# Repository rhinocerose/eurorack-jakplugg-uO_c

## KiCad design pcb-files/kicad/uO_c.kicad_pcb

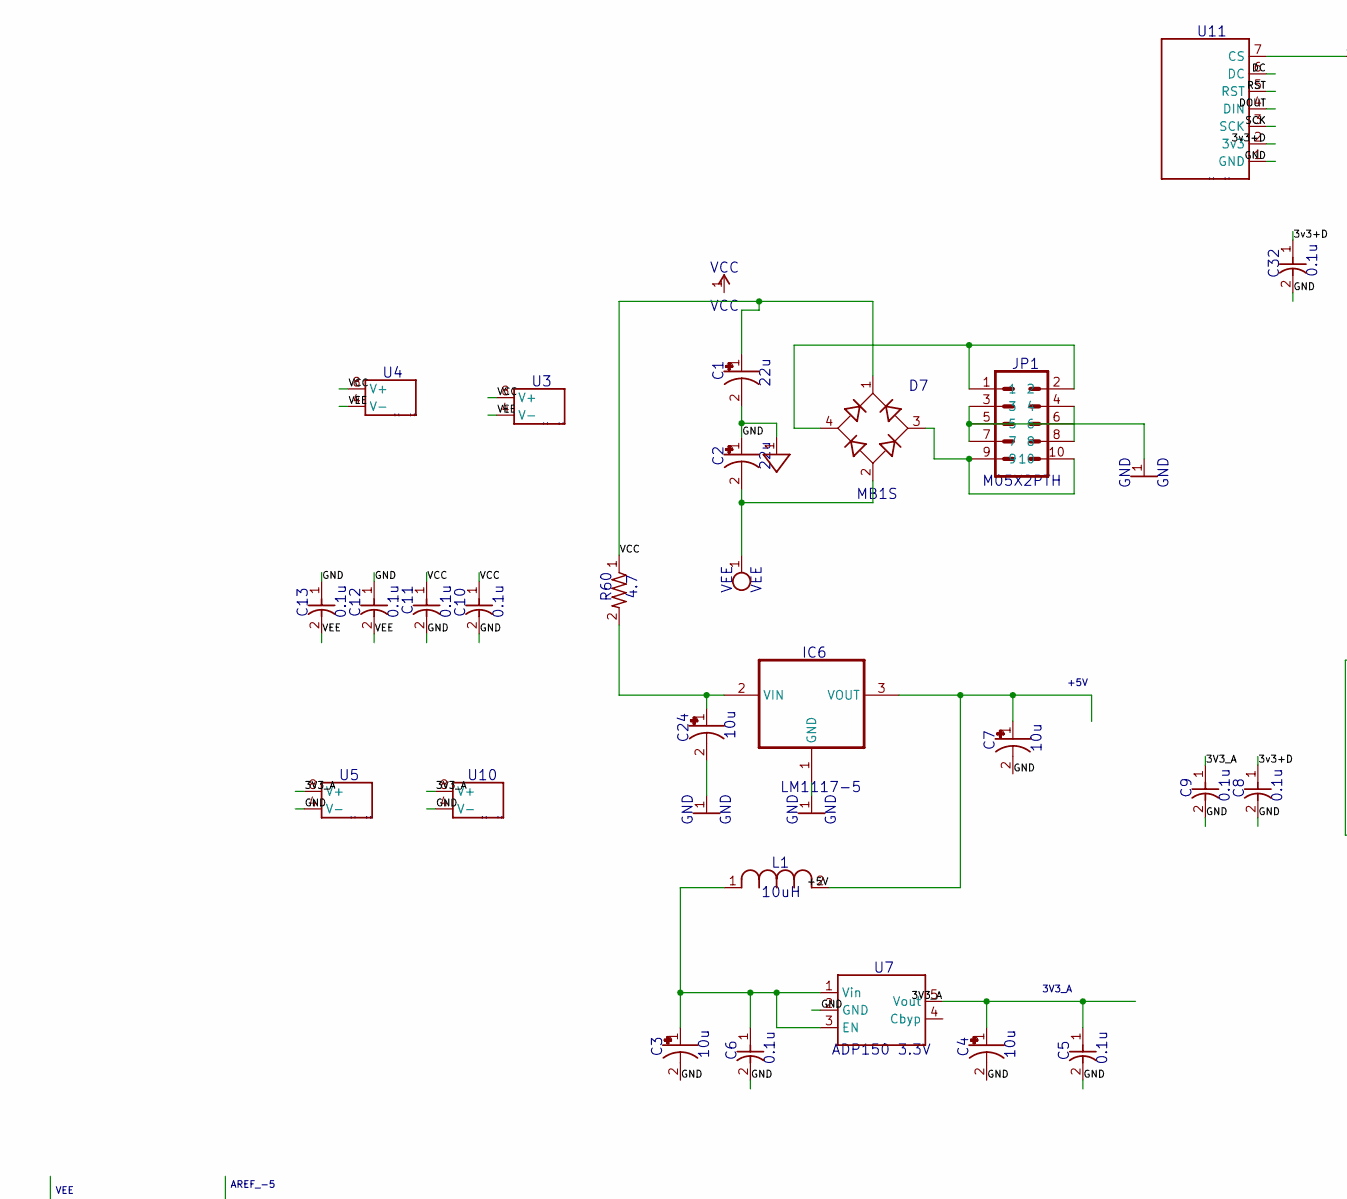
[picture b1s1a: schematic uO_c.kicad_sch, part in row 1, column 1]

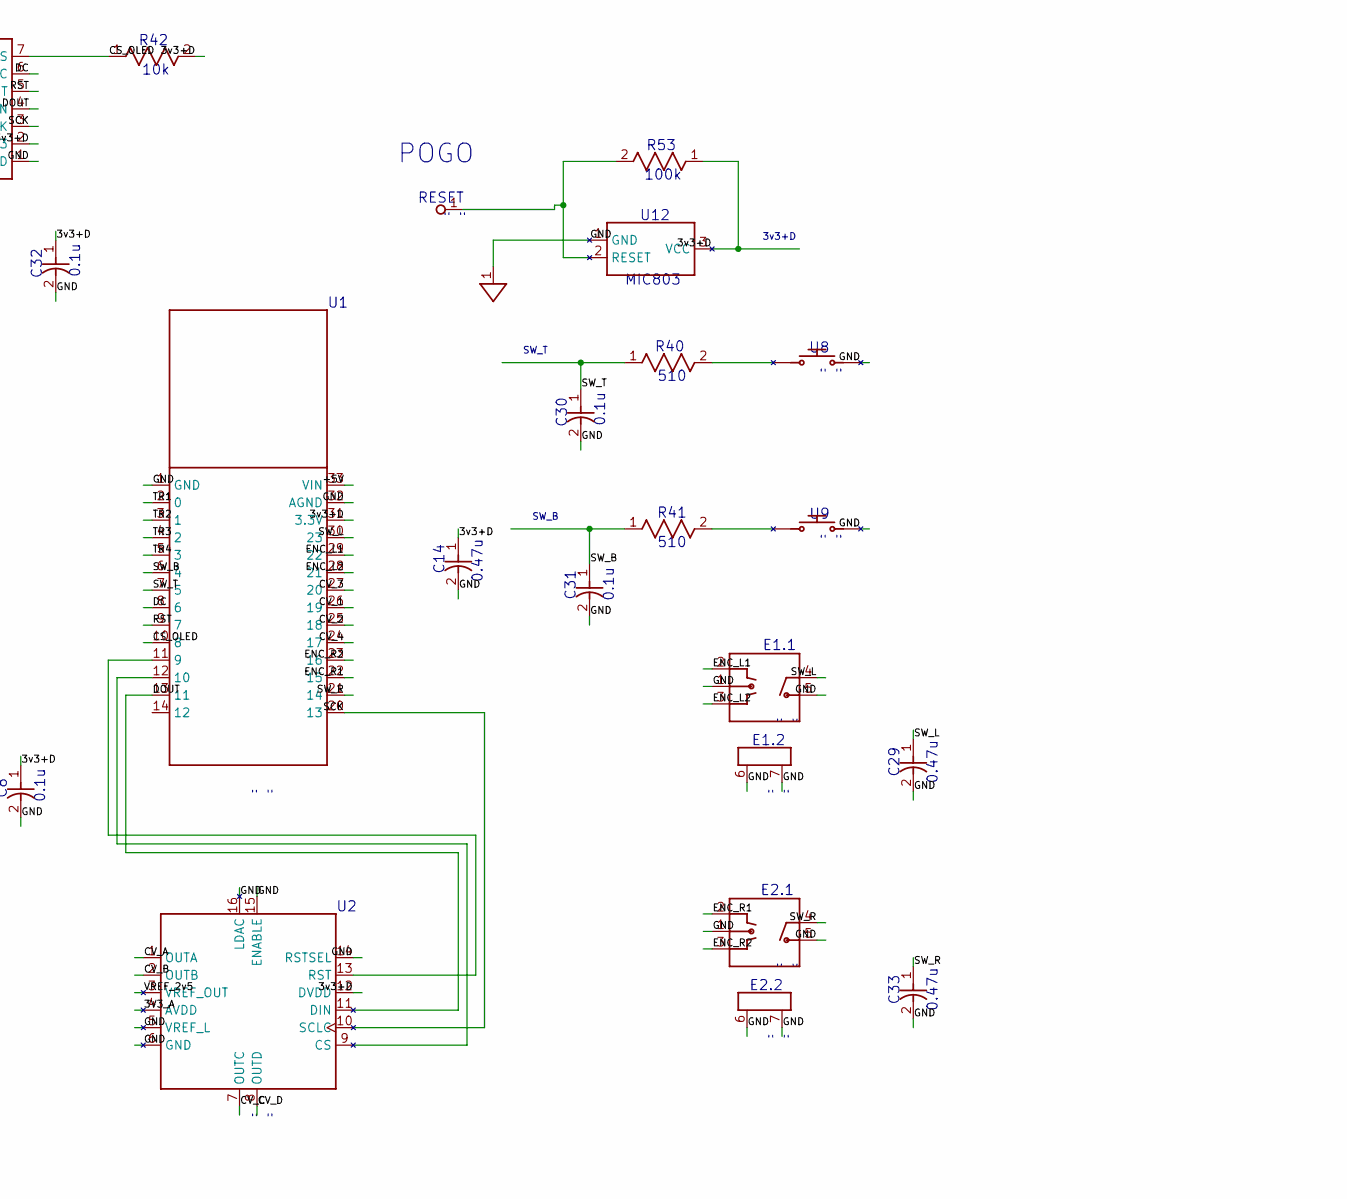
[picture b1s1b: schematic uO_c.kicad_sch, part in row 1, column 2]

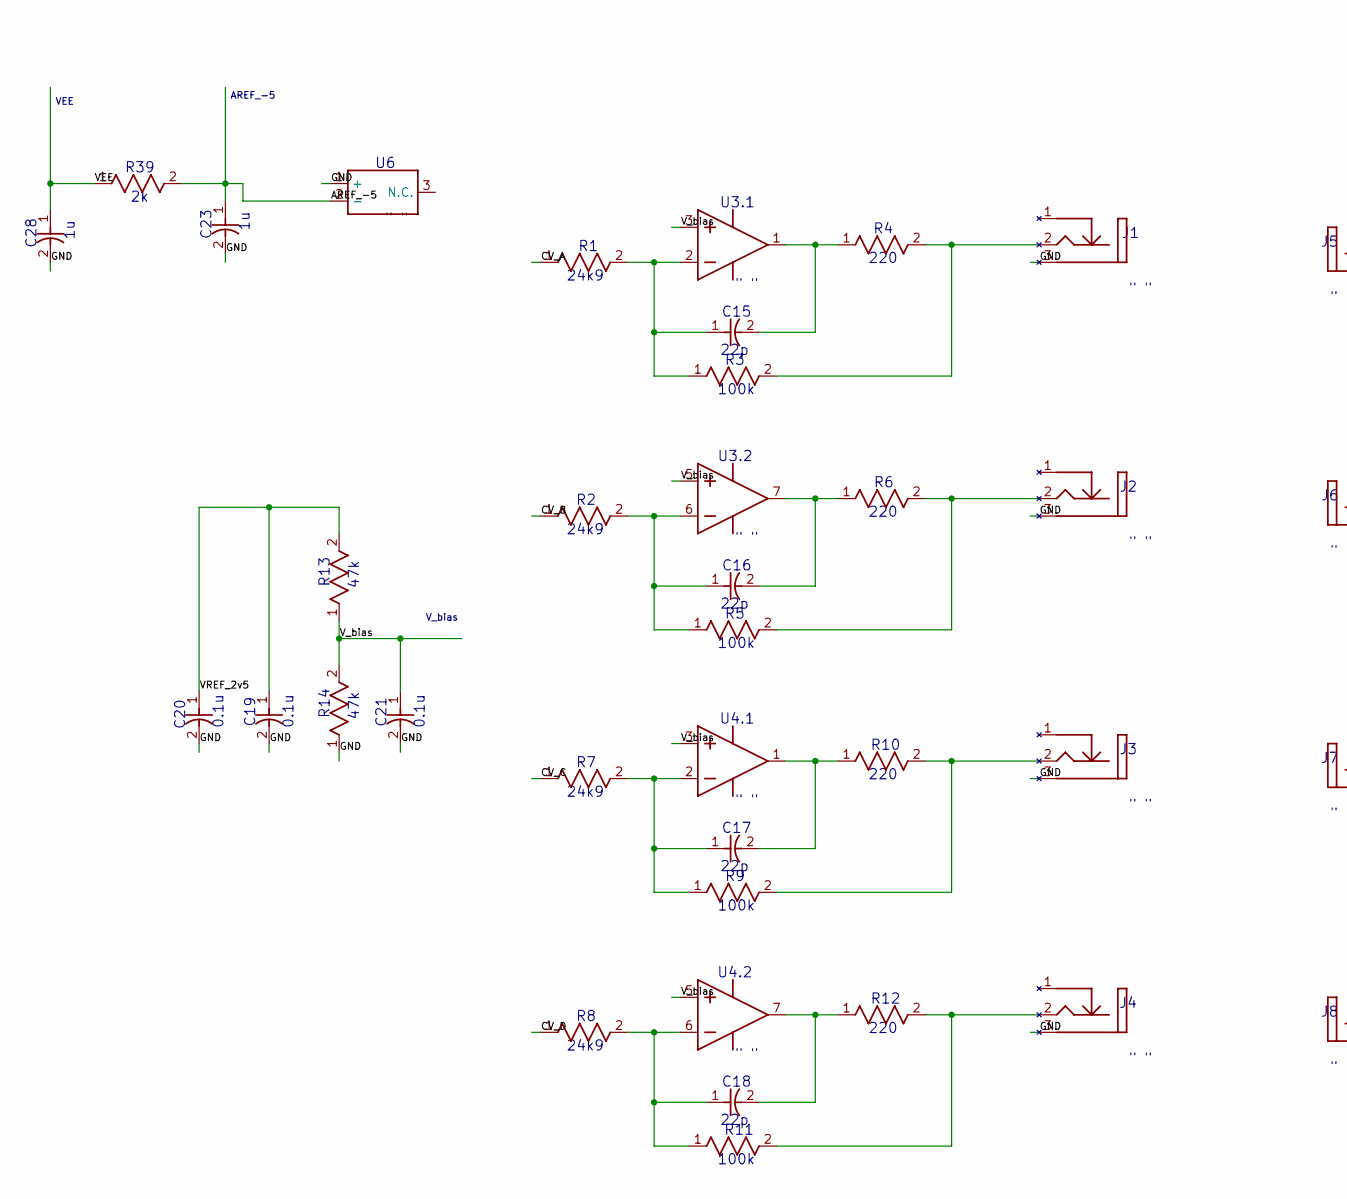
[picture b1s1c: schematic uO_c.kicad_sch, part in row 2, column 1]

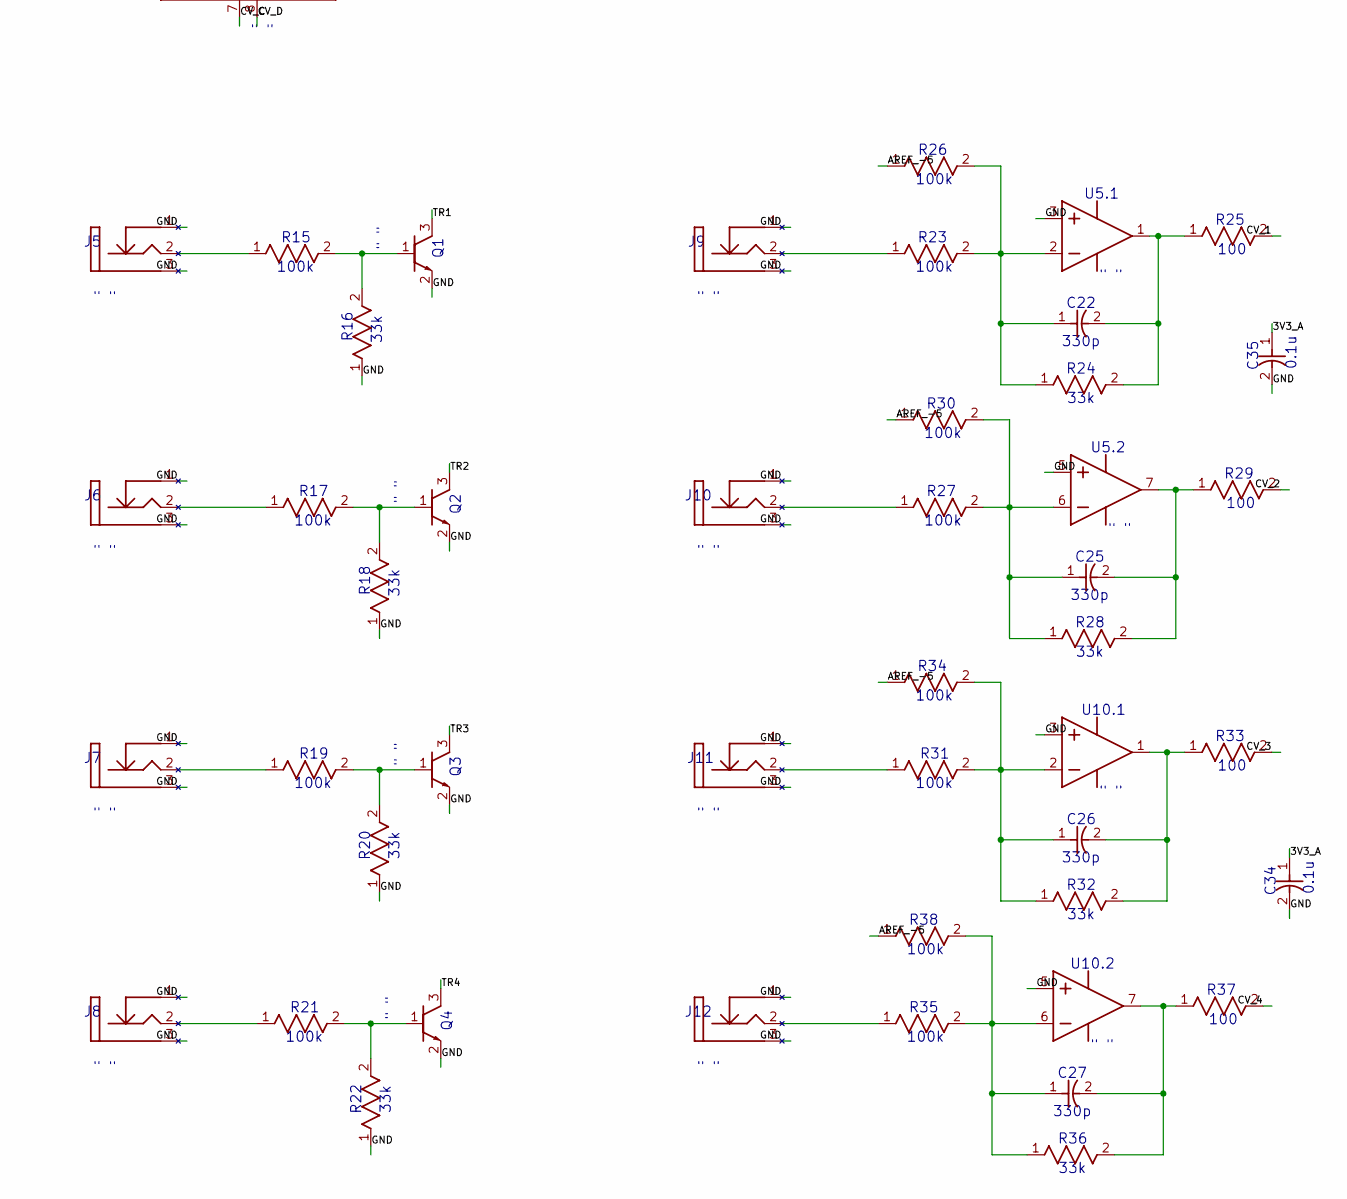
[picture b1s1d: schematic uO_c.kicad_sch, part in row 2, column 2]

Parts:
C1, C2: 22u; CAPAE-5.3X5.3H3
C3, C4, C7, C24: 10u; CAPAE-5.3X5.3H3
C5, C6, C8, C9, C10, C11, C12, C13, C19, C20, C21, C30, C31, C32, C34, C35: 0.1u; CAP_0805
C14, C29, C33: 0.47u; CAP_0805
C15, C16, C17, C18: 22p; CAP_0805
C22, C25, C26, C27: 330p; CAP_0805
C23, C28: 1u; CAP_0805
D7: MB1S; SOP-4_6.5X2.54
E1, E2: PEC11
IC6: LM1117-5; TO252
J1, J2, J3, J4: THONKICONN; THONKICONN_JACK
J5, J6, J7, J8, J9, J10, J11, J12: THONKICONN_20; THONKICONN_JACK
JP1: M05X2PTH; AVR_ICSP
L1: 10uH; RES_1210
Q1, Q2, Q3, Q4: MMBT3904; SOT23
R1, R2, R7, R8: 24k9; RES_0805
R3, R5, R9, R11, R15, R17, R19, R21, R23, R26, R27, R30, R31, R34, R35, R38, R53: 100k; RES_0805
R4, R6, R10, R12: 220; RES_0805
R13, R14: 47k; RES_0805
R16, R18, R20, R22, R24, R28, R32, R36: 33k; RES_0805
R25, R29, R33, R37: 100; RES_0805
R39: 2k; RES_0805
R40, R41: 510; RES_0805
R42: 10k; RES_0805
R60: 4.7; R1206
RESET0: RESET; ROUND-ROUND
U1: TEENSY_3.1_EDGE; TEENSY3.1_EDGE
U2: DAC8565; TSSOP-16
U3, U4: OPA2172; SOIC-8_150MIL
U5, U10: MCP6002; SOIC-8_150MIL
U6: LM4040_EM3-5.0; SOT23
U7: ADP150 3.3V; SOT23-5
U8, U9: 6MM_TACTILE_SW; TL1105SP
U11: 1306_DISP_O_C
U12: MIC803; SOT23

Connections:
3V3_A: C4.1 (+), C5.1, C9.1, C34.1, C35.1, U2.4 (AVDD), U5.8 (V+), U7.5 (Vout), U10.8 (V+)
3v3+D: C8.1, C14.1, C32.1, R42.2, R53.1, U1.31 (3.3V), U2.12 (DVDD), U11.2 (3v3), U12.3 (VCC)
+5V: C7.1 (+), IC6.3 (VOUT), L1.2, U1.33 (VIN)
AREF_-5: C23.1, R26.1, R30.1, R34.1, R38.1, R39.2, U6.2 (-)
CS_DAC: U1.12 (10), U2.9 (CS)
CS_OLED: R42.1, U1.10 (8), U11.7 (CS)
CV_1: R25.2, U1.26 (19)
CV_2: R29.2, U1.25 (18)
CV_3: R33.2, U1.27 (20)
CV_4: R37.2, U1.24 (17)
CV_A: R1.1, U2.1 (OUTA)
CV_B: R2.1, U2.2 (OUTB)
CV_C: R7.1, U2.7 (OUTC)
CV_D: R8.1, U2.8 (OUTD)
DC: U1.8 (6), U11.6 (DC)
DOUT: U1.13 (11), U2.11 (DIN), U11.4 (DIN)
ENC_L1: E1.2, U1.29 (22)
ENC_L2: E1.3, U1.28 (21)
ENC_R1: E2.2, U1.22 (15)
ENC_R2: E2.3, U1.23 (16)
unnamed: D7.3 (AC2), JP1.9, JP1.10
Net_0: J2.2 (Tip), R5.2, R6.2
Net_1: C16.1, R2.2, R5.1, U3.6 (IN-)
Net_2: C16.2, R6.1, U3.7 (OUT)
Net_3: J3.2 (Tip), R9.2, R10.2
Net_4: C17.1, R7.2, R9.1, U4.2 (IN-)
Net_5: C17.2, R10.1, U4.1 (OUT)
Net_6: J4.2 (Tip), R11.2, R12.2
Net_7: C18.1, R8.2, R11.1, U4.6 (IN-)
Net_8: C18.2, R12.1, U4.7 (OUT)
Net_9: Q2.1 ((B)), R17.2, R18.2
Net_10: Q3.1 ((B)), R19.2, R20.2
Net_11: Q4.1 ((B)), R21.2, R22.2
Net_12: C25.1, R27.2, R28.1, R30.2, U5.6 (IN-)
Net_13: C3.1 (+), C6.1, L1.1, U7.1 (Vin), U7.3 (EN)
Net_18: C26.1, R31.2, R32.1, R34.2, U10.2 (IN-)
Net_19: J1.2 (Tip), R3.2, R4.2
Net_20: C15.1, R1.2, R3.1, U3.2 (IN-)
Net_21: C15.2, R4.1, U3.1 (OUT)
Net_22: C27.1, R35.2, R36.1, R38.2, U10.6 (IN-)
Net_35: Q1.1 ((B)), R15.2, R16.2
Net_39: J8.2 (Tip), R21.1
Net_40: J7.2 (Tip), R19.1
Net_41: J6.2 (Tip), R17.1
Net_42: J5.2 (Tip), R15.1
Net_43: C22.1, R23.2, R24.1, R26.2, U5.2 (IN-)
Net_48: C27.2, R36.2, R37.1, U10.7 (OUT)
Net_49: C26.2, R32.2, R33.1, U10.1 (OUT)
Net_50: C25.2, R28.2, R29.1, U5.7 (OUT)
Net_51: C22.2, R24.2, R25.1, U5.1 (OUT)
Net_52: J9.2 (Tip), R23.1
Net_53: J10.2 (Tip), R27.1
Net_54: J11.2 (Tip), R31.1
Net_55: J12.2 (Tip), R35.1
Net_73: C24.1 (+), IC6.2 (VIN), R60.2
Net_75: R41.2, U9.1, U9.2 (1)
Net_76: R40.2, U8.1, U8.2 (1)
Net_88: R53.2, RESET0.1, U12.2 (RESET)
Net_107: D7.4 (AC1), JP1.1, JP1.2
RST: U1.9 (7), U11.5 (RST)
RST_DAC: U1.11 (9), U2.13 (RST)
SCK: U1.20 (13), U2.10 (SCLC), U11.3 (SCK)
SW_B: C31.1, R41.1, U1.6 (4)
SW_L: C29.1, E1.4, U1.30 (23)
SW_R: C33.1, E2.4, U1.21 (14)
SW_T: C30.1, R40.1, U1.7 (5)
TR1: Q1.3 ((C)), U1.2 (0)
TR2: Q2.3 ((C)), U1.3 (1)
TR3: Q3.3 ((C)), U1.4 (2)
TR4: Q4.3 ((C)), U1.5 (3)
VCC: C1.1 (+), C10.1, C11.1, D7.1 (+), R60.1, U3.8 (V+), U4.8 (V+)
VEE: C2.2 (-), C12.2, C13.2, C28.1, D7.2 (-), R39.1, U3.4 (V-), U4.4 (V-)
VREF_2v5: C19.1, C20.1, R13.2, U2.3 (VREF_OUT)
V_bias: C21.1, R13.1, R14.2, U3.3 (IN+), U3.5 (IN+), U4.3 (IN+), U4.5 (IN+)

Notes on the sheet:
E1.1
220
" "
0.1u
V_bias
U4.2
100k
R34
R60
10u
47k
R35
VCC
33k
R41
GND
U12
E2.1
C30
10uH
R30
VEE
C19
R32
C34
3v3+D
4.7
R22
R11
C26
C21
U11
0.47u
R14
C14
C10
SW_B
22u
R40
100

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
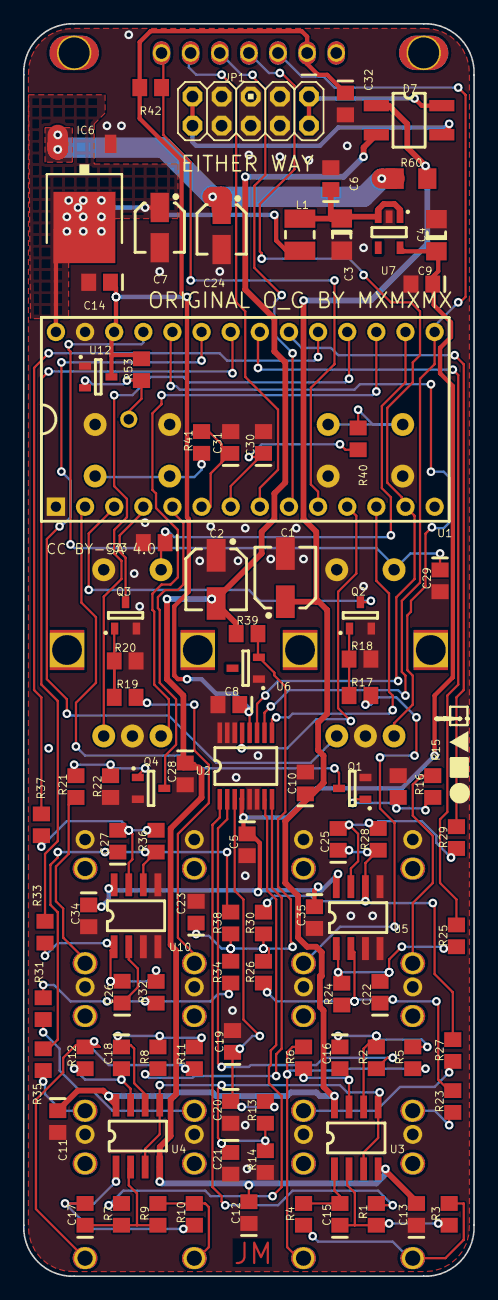
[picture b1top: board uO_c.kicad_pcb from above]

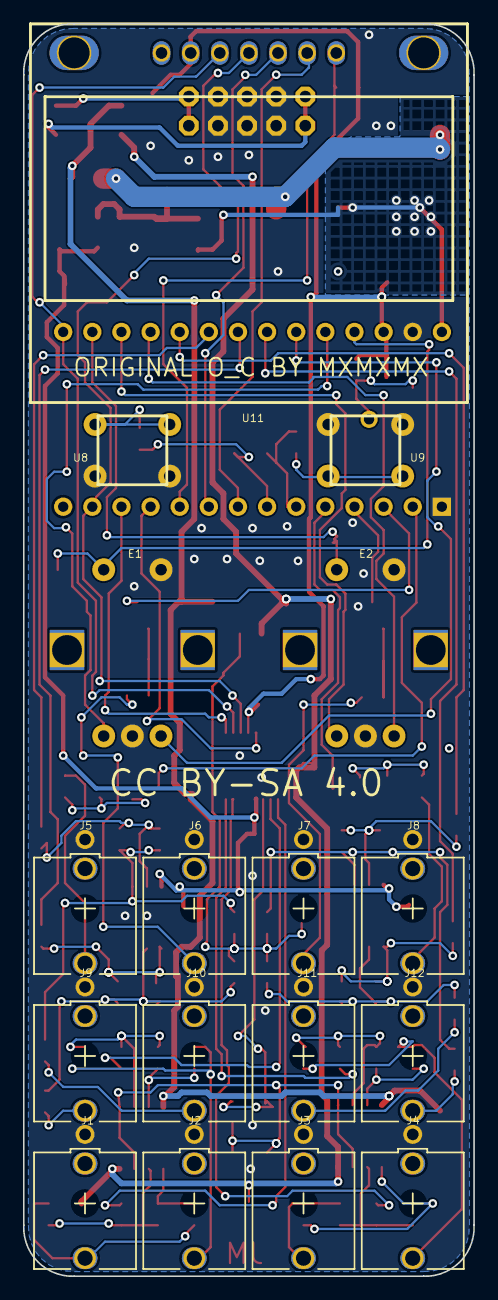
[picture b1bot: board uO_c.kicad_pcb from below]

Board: 2 copper layers, 39.3 x 109.2 mm, 116 parts (17 on the bottom side), 75 nets.

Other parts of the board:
Pad1, Pad2: PAD; Pad

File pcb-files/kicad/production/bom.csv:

Designator,Footprint,Quantity,Value,LCSC Part #
C1,CAPAE-5.3x5.3h3,1,22u,
"C10, C12, C13, C19, C30, C31",CAP_0805_C10,6,0.1u,
C11,CAP_0805_C11,1,0.1u,
C14,CAP_0805_C14,1,0.47u,
"C15, C17",CAP_0805_C10,2,22p,
"C16, C18",CAP_0805,2,22p,
C2,CAPAE-5.3x5.3h3_C2,1,22u,
"C20, C21, C34, C35, C5, C8, C9",CAP_0805,7,0.1u,
"C22, C25, C26, C27",CAP_0805_C10,4,330p,
C23,CAP_0805_C23,1,1u,
C24,CAPAE-4.3x4.3h5.4_C24,1,10u,
C28,CAP_0805,1,1u,
C29,CAP_0805,1,0.47u,
C3,CAP_1206,1,10u,
C32,CAP_0805_C32,1,0.1u,
C33,CAP_0805_C33,1,0.47u,
C4,CAP_1206_C4,1,10u,
C6,CAP_0805_C6,1,0.1u,
C7,CAPAE-4.3x4.3h5.4,1,10u,
D7,SOP-4_6.5x2.54,1,MB1S,
"E1, E2",PEC11,2,PEC11,
IC6,TO252,1,LM1117-5,
"J1, J10, J11, J12, J2, J3, J4, J5, J6, J7, J8, J9",Thonkiconn_Jack,12,THONKICONN,
JP1,AVR_ICSP,1,M05X2PTH,
L1,RES_1210,1,10uH,
"PAD1, PAD2",Pad,2,PAD,
Q1,SOT23,1,MMBT3904,
"Q2, Q3",SOT23_Q2,2,MMBT3904,
Q4,SOT23_Q4,1,MMBT3904,
"R1, R7",RES_0805,2,24k9,
"R10, R12, R6",RES_0805_R2,3,220,
"R11, R17, R19, R5, R53",RES_0805,5,100k,
"R13, R14",RES_0805_R2,2,47k,
R15,RES_0805_R15,1,100k,
R16,RES_0805_R16,1,33k,
"R18, R20",RES_0805,2,33k,
"R2, R8",RES_0805_R2,2,24k9,
"R21, R23, R27, R3, R9",RES_0805_R2,5,100k,
"R22, R24, R28, R32, R36",RES_0805_R2,5,33k,
"R25, R29",RES_0805_R2,2,100,
"R26, R34",RES_0805,2,75k,
"R30, R38",RES_0805_R2,2,75k,
R31,RES_0805_R31,1,100k,
"R33, R37",RES_0805_R31,2,100,
R35,RES_0805_R35,1,100k,
R39,RES_0805_R2,1,2k,
R4,RES_0805,1,220,
R40,RES_0805_R40,1,510,
R41,RES_0805,1,510,
R42,RES_0805_R16,1,10k,
R60,R1206,1,4.7,
RESET0,Round-Round,1,RESET,
U1,Teensy3.1_edge,1,TEENSY 3.1_EDGE,
U10,SOIC-8_150mil_U10,1,MCP6002,
U11,1306_disp_O_C,1,1306_DISP_O_C,
U12,SOT23_Q4,1,MIC803,
U2,TSSOP-16,1,DAC8565,
"U3, U4",SOIC-8_150mil,2,OPA2172,
U5,SOIC-8_150mil,1,MCP6002,
U6,SOT23_U6,1,LM4040_EM3-5.0,
U7,SOT23-5,1,ADP150 3.3V,
U8,TL1105SP,1,6MM TACTILE SW,
U9,TL1105SP_U9,1,6MM TACTILE SW,

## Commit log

2025-08-10 Kicad

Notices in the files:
pcb-files/kicad/uO_c.kicad_pcb:
CC BY-SA 4.0
